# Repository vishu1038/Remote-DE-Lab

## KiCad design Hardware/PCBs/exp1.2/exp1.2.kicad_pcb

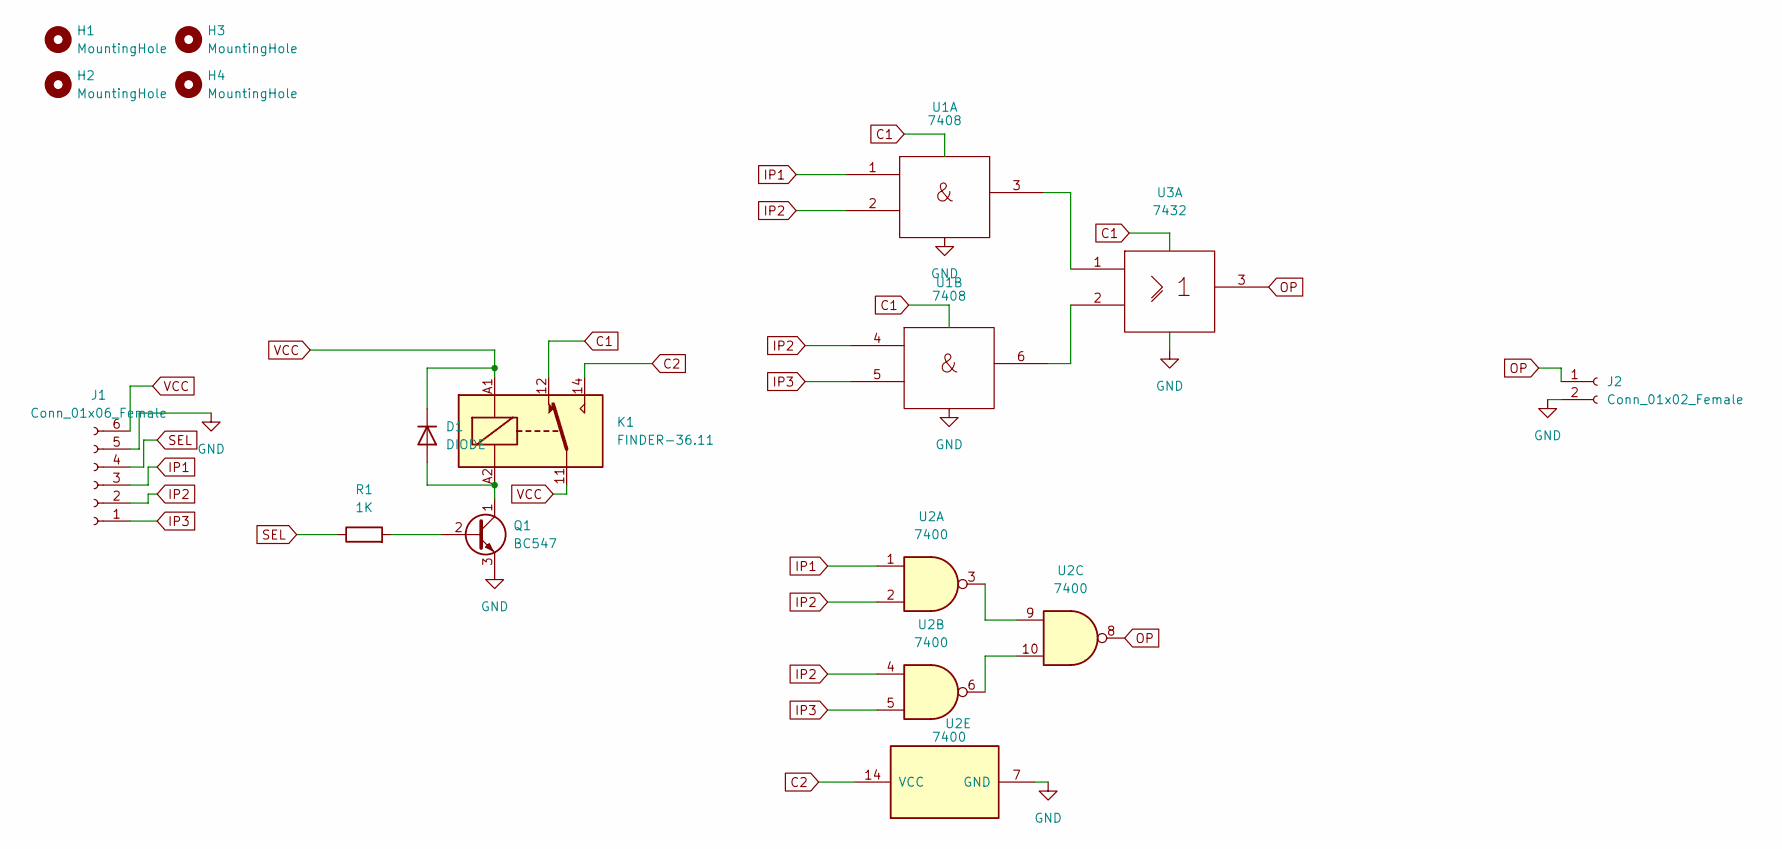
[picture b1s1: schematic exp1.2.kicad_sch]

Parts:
D1: DIODE; D_MiniMELF
H1, H2, H3, H4: MountingHole; MountingHole_2.1mm
J1: Conn_01x06_Female; JST_EH_S6B-EH_1x06_P2.50mm_Horizontal
J2: Conn_01x02_Female; JST_EH_S2B-EH_1x02_P2.50mm_Horizontal
K1: FINDER-36.11; Relay_SPDT_Finder_36.11
Q1: BC547; TO-92_Inline
R1: 1K; R_Axial_DIN0207_L6.3mm_D2.5mm_P7.62mm_Horizontal
U1: 7408; DIP-14_W7.62mm_Socket
U2: 7400; DIP-14_W7.62mm_Socket
U3: 7432; DIP-14_W7.62mm_Socket

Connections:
C1: K1.12, U1.14 (Vcc), U3.14 (Vcc)
C2: K1.14, U2.14 (VCC)
GND: J1.5, J2.2, Q1.3 (E), U1.7 (Gnd), U2.7 (GND), U3.7 (Gnd)
IP1: J1.3, U1.1, U2.1
IP2: J1.2, U1.2, U1.4, U2.2, U2.4
IP3: J1.1, U1.5, U2.5
unnamed: D1.1 (A), K1.A2, Q1.1 (C)
unnamed: Q1.2 (B), R1.2
unnamed: U1.3, U3.1
unnamed: U1.6, U3.2
unnamed: U2.3, U2.9
unnamed: U2.6, U2.10
OP: J2.1, U2.8, U3.3
SEL: J1.4, R1.1
VCC: D1.2 (K), J1.6, K1.11, K1.A1

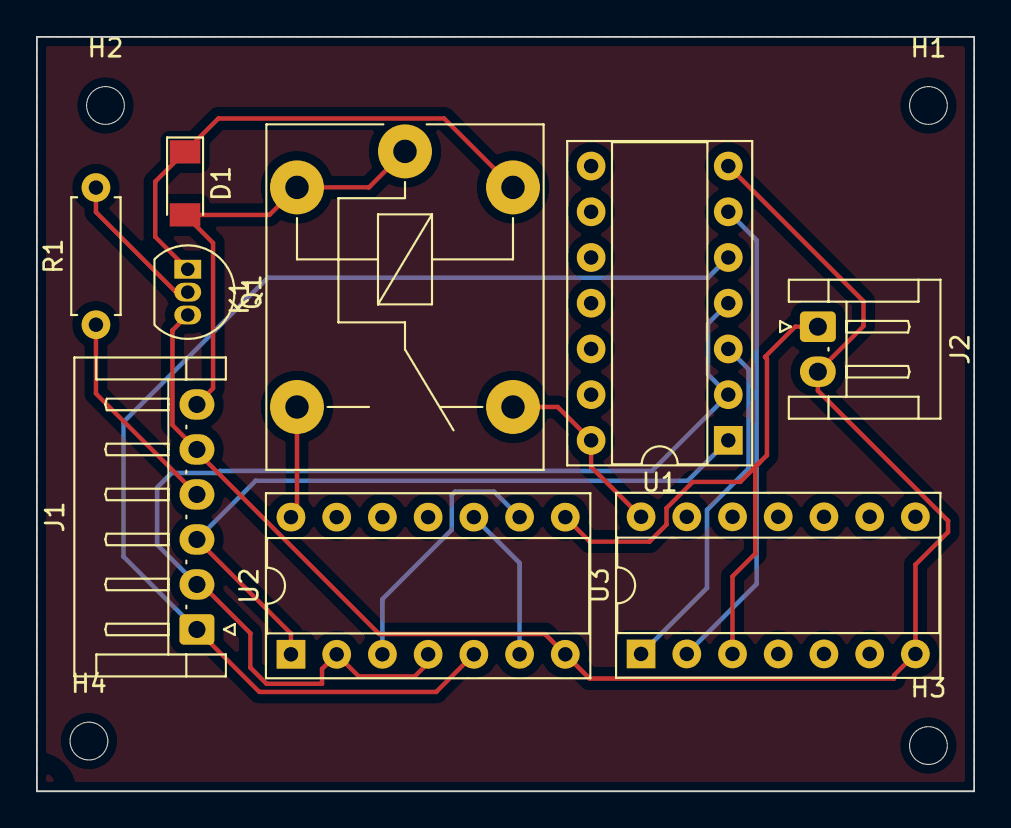
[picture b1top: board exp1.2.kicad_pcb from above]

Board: 2 copper layers, 52.1 x 41.9 mm, 13 parts (0 on the bottom side), 15 nets.

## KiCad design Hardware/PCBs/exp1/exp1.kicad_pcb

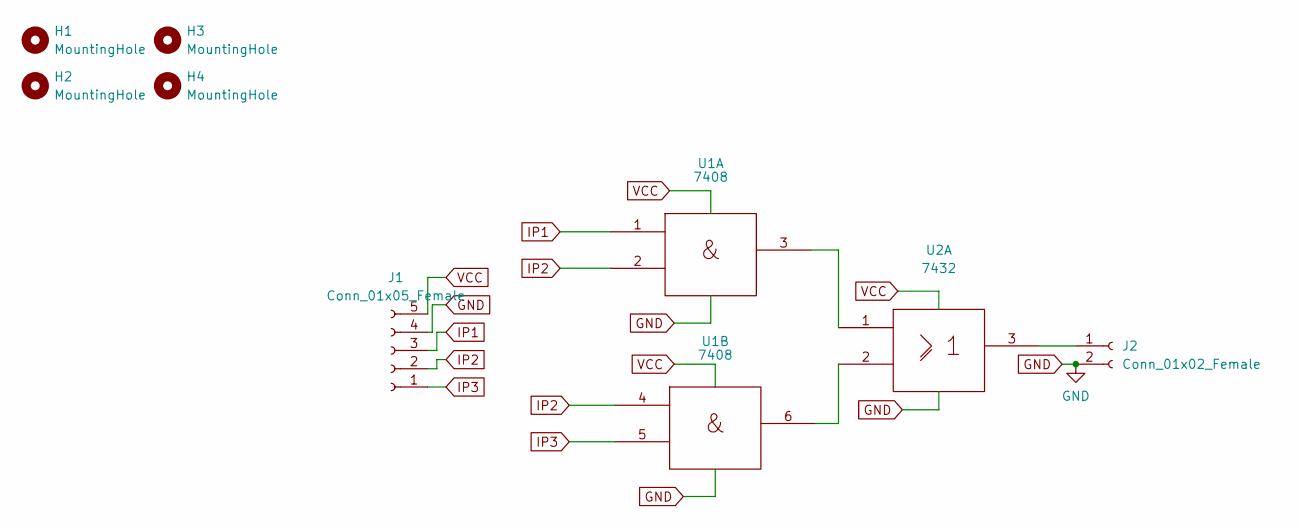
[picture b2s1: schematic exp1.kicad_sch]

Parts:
H1, H2, H3, H4: MountingHole; MountingHole_2.5mm
J1: Conn_01x05_Female; JST_EH_S5B-EH_1x05_P2.50mm_Horizontal
J2: Conn_01x02_Female; JST_EH_S2B-EH_1x02_P2.50mm_Horizontal
U1: 7408; DIP-14_W7.62mm_Socket
U2: 7432; DIP-14_W7.62mm_Socket

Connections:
GND: J1.4, J2.2, U1.7 (Gnd), U2.7 (Gnd)
IP1: J1.3, U1.1
IP2: J1.2, U1.2, U1.4
IP3: J1.1, U1.5
unnamed: J2.1, U2.3
unnamed: U1.3, U2.1
unnamed: U1.6, U2.2
VCC: J1.5, U1.14 (Vcc), U2.14 (Vcc)

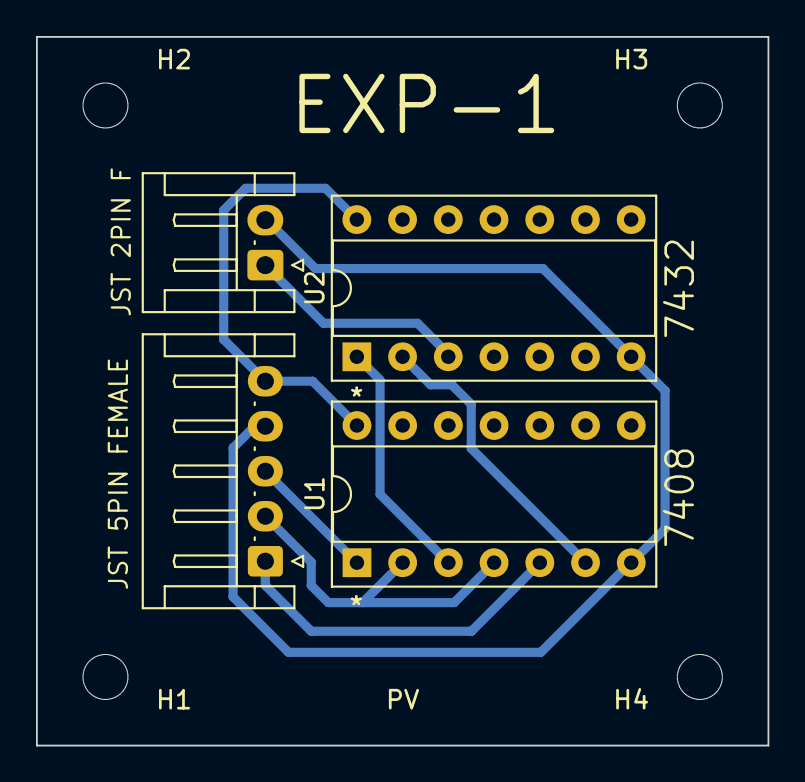
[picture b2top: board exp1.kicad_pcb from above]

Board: 2 copper layers, 40.6 x 39.4 mm, 8 parts (0 on the bottom side), 8 nets.

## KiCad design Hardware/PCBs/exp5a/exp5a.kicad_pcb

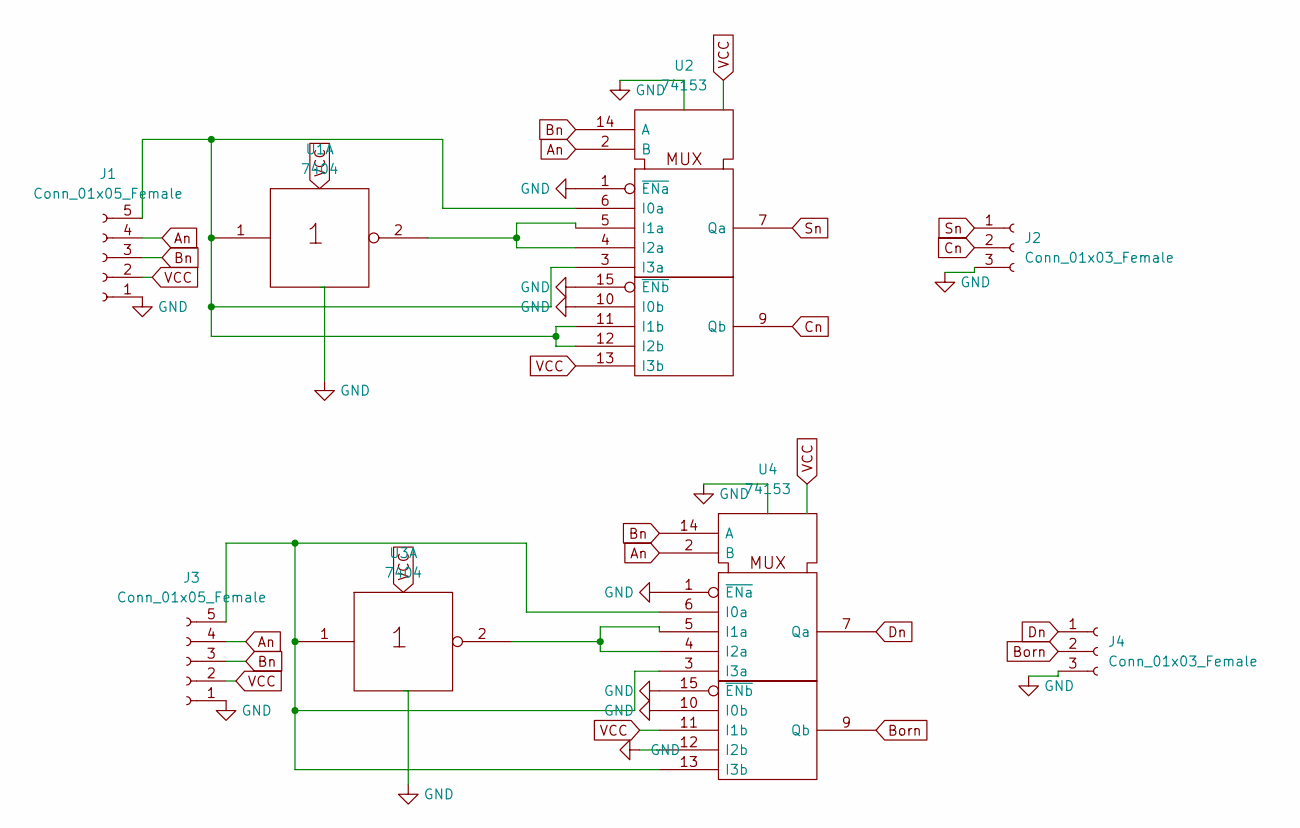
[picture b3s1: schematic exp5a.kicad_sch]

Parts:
J1, J3: Conn_01x05_Female; JST_EH_S5B-EH_1x05_P2.50mm_Horizontal
J2, J4: Conn_01x03_Female; JST_EH_S3B-EH_1x03_P2.50mm_Horizontal
U1, U3: 7404; DIP-14_W7.62mm_Socket
U2, U4: 74153; DIP-16_W7.62mm_Socket

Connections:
An: J1.4, J3.4, U2.2 (B), U4.2 (B)
Bn: J1.3, J3.3, U2.14 (A), U4.14 (A)
Born: J4.2, U4.9 (Qb)
Cn: J2.2, U2.9 (Qb)
Dn: J4.1, U4.7 (Qa)
GND: J1.1, J2.3, J3.1, J4.3, U1.7 (Gnd), U2.1 (~ENa), U2.8 (GND), U2.10 (I0b), U2.15 (~ENb), U3.7 (Gnd), U4.1 (~ENa), U4.8 (GND), U4.10 (I0b), U4.12 (I2b), U4.15 (~ENb)
unnamed: J1.5, U1.1, U2.3 (I3a), U2.6 (I0a), U2.11 (I1b), U2.12 (I2b)
unnamed: J3.5, U3.1, U4.3 (I3a), U4.6 (I0a), U4.13 (I3b)
unnamed: U1.2, U2.4 (I2a), U2.5 (I1a)
unnamed: U3.2, U4.4 (I2a), U4.5 (I1a)
Sn: J2.1, U2.7 (Qa)
VCC: J1.2, J3.2, U1.14 (Vcc), U2.13 (I3b), U2.16 (VCC), U3.14 (Vcc), U4.11 (I1b), U4.16 (VCC)

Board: 2 copper layers, 8 parts (0 on the bottom side), 12 nets, no tracks yet.
